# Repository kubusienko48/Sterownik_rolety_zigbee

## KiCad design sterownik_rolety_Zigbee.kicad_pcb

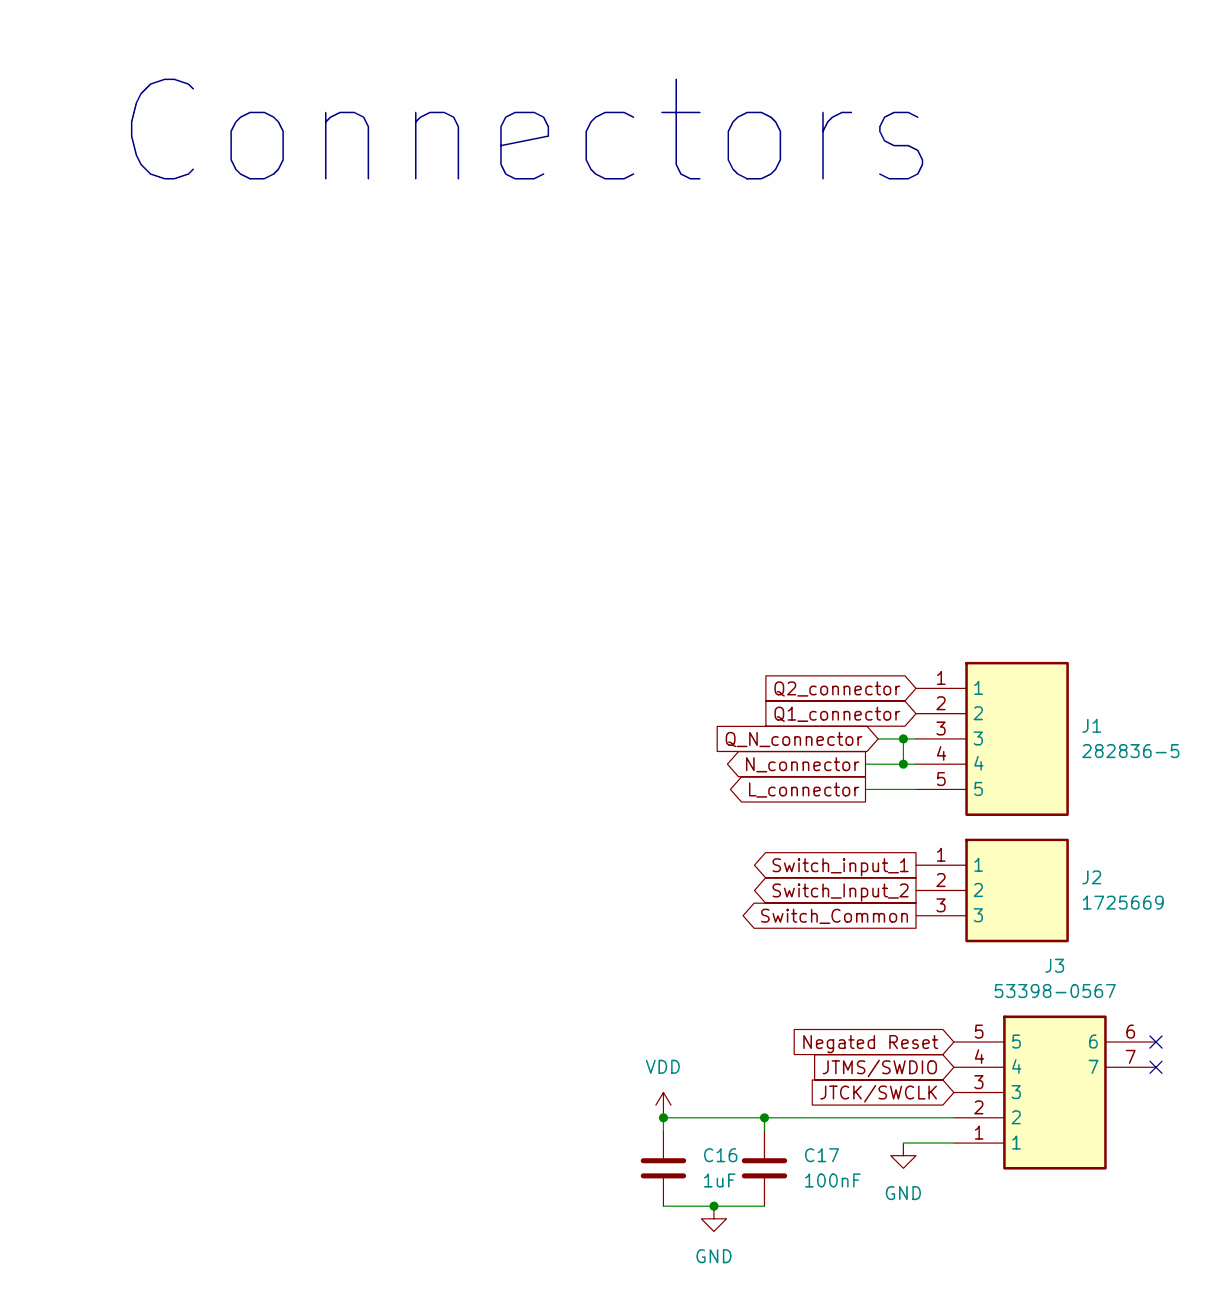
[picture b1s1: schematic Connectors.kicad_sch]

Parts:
C16: 1uF; C_0201_0603Metric
C17: 100nF; C_0201_0603Metric
J1: 282836-5; 2828365; Mouser Part Number 571-2828365
J2: 1725669; Mouser Part Number 651-1725669
J3: 53398-0567; 533980567; Mouser Part Number 538-53398-0567

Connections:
GND: C16.2, C17.2, J3.1; also elsewhere on the board
JTCK/SWCLK: J3.3; also elsewhere on the board
JTMS/SWDIO: J3.4; also elsewhere on the board
L_connector: J1.5; also elsewhere on the board
N_connector: J1.3, J1.4; also elsewhere on the board
Negated Reset: J3.5; also elsewhere on the board
Q1_connector: J1.2; also elsewhere on the board
Q2_connector: J1.1; also elsewhere on the board
Switch_Common: J2.3; also elsewhere on the board
Switch_Input_2: J2.2; also elsewhere on the board
Switch_input_1: J2.1; also elsewhere on the board
VDD: C16.1, C17.1, J3.2; also elsewhere on the board

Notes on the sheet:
Connectors

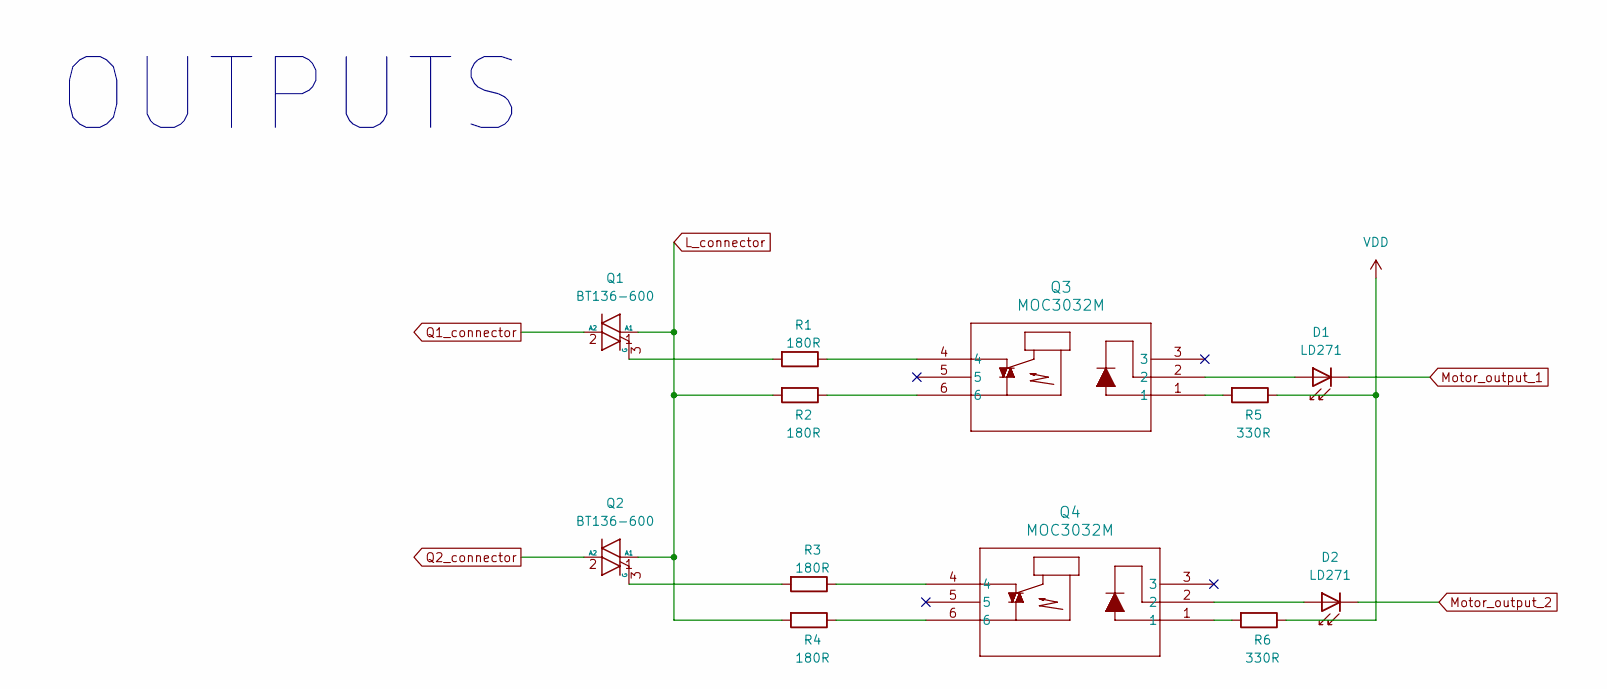
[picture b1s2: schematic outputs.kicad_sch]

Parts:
D1, D2: LD271; LED_D5.0mm_IRGrey
Q1, Q2: BT136-600; TO-220-3_Vertical
Q3, Q4: MOC3032M; DIP-6_W7.62mm
R1, R2, R3, R4: 180R; R_0201_0603Metric
R5, R6: 330R; R_0201_0603Metric

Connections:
L_connector: Q1.1 (A1), Q2.1 (A1), R2.2, R4.2; also elsewhere on the board
Motor_output_1: D1.1 (K); also elsewhere on the board
Motor_output_2: D2.1 (K); also elsewhere on the board
unnamed: D1.2 (A), Q3.2
unnamed: D2.2 (A), Q4.2
unnamed: Q1.3 (G), R1.2
unnamed: Q2.3 (G), R3.2
unnamed: Q3.1, R5.2
unnamed: Q3.4, R1.1
unnamed: Q3.6, R2.1
unnamed: Q4.1, R6.2
unnamed: Q4.4, R3.1
unnamed: Q4.6, R4.1
Q1_connector: Q1.2 (A2); also elsewhere on the board
Q2_connector: Q2.2 (A2); also elsewhere on the board
VDD: R5.1, R6.1; also elsewhere on the board

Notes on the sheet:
OUTPUTS

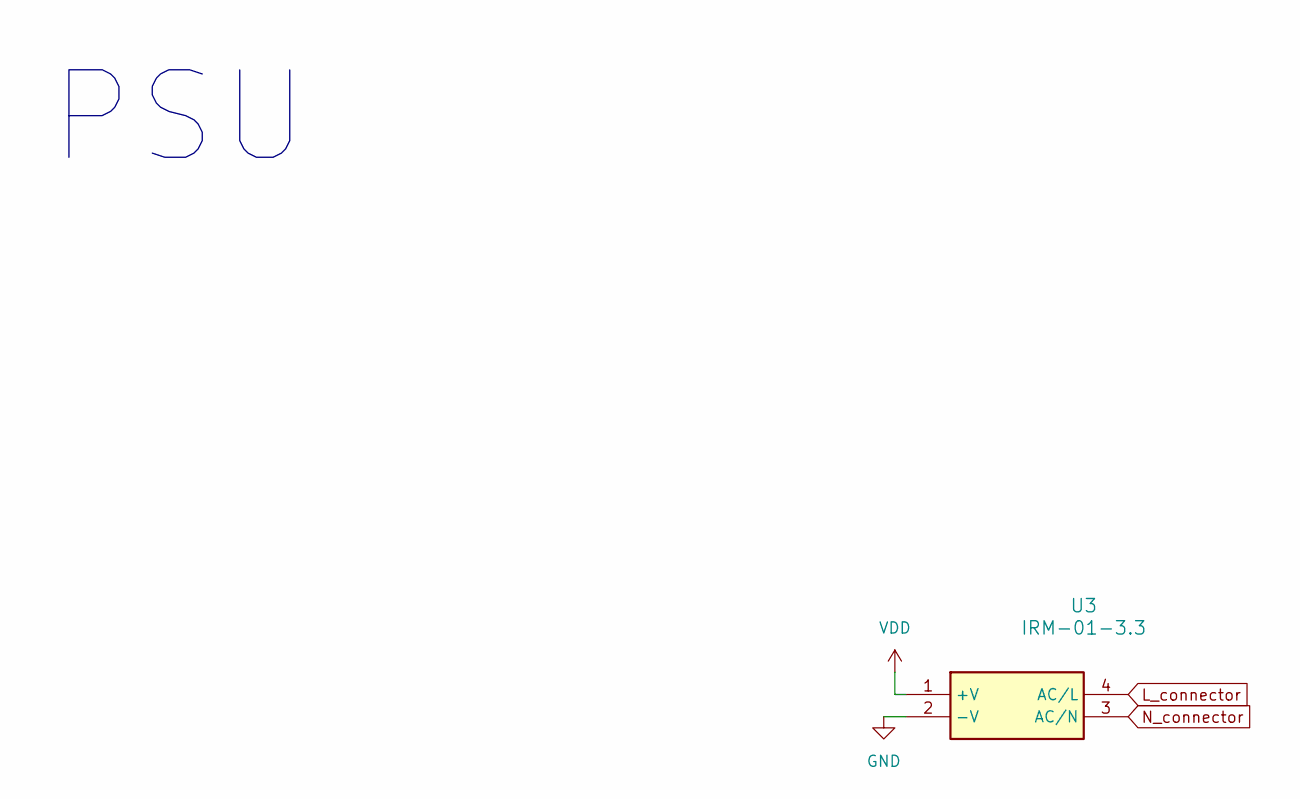
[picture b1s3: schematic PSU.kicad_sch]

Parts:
U3: IRM-01-3.3; IRM015; Mouser Part Number 709-IRM01-3.3

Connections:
GND: U3.2 (-V); also elsewhere on the board
L_connector: U3.4 (AC/L); also elsewhere on the board
N_connector: U3.3 (AC/N); also elsewhere on the board
VDD: U3.1 (+V); also elsewhere on the board

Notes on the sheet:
PSU

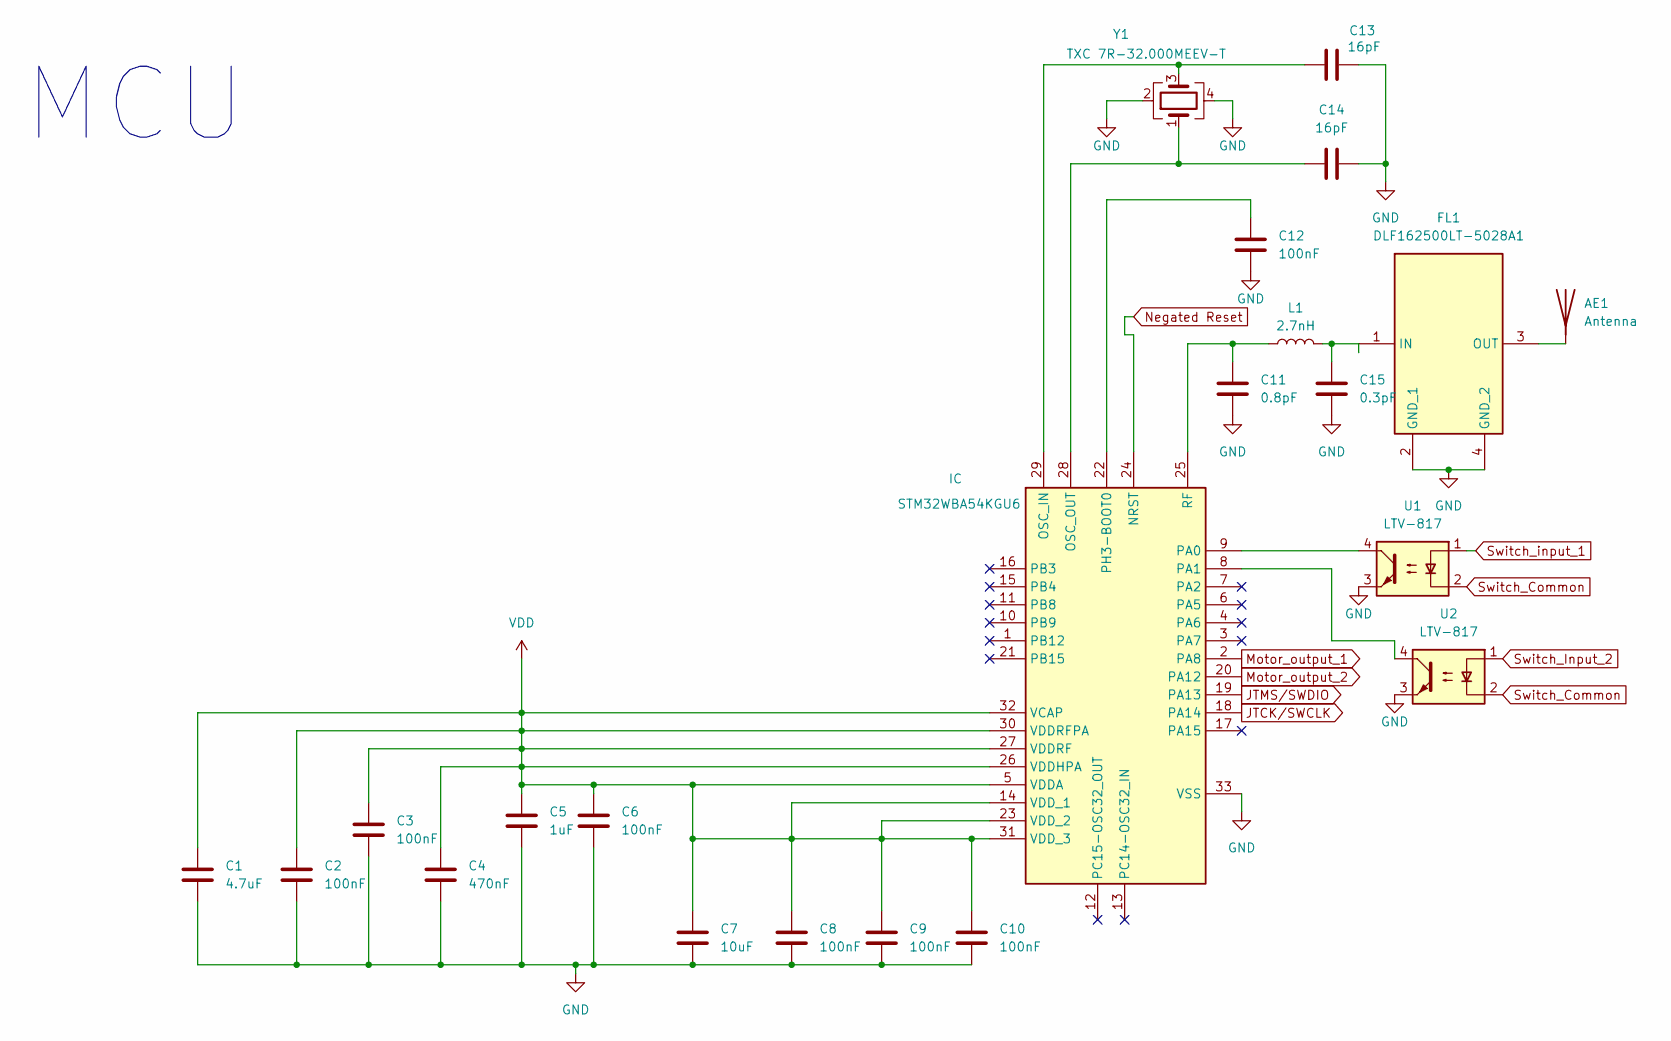
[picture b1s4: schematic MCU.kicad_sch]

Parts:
111111111: STM32WBA54KGU6; QFN50P500X500X60-33N-D; Mouser Part Number 511-STM32WBA54KGU6
AE1: Antenna
C1: 4.7uF; C_0201_0603Metric
C2, C3, C6, C8, C9, C10, C12: 100nF; C_0201_0603Metric
C4: 470nF; C_0201_0603Metric
C5: 1uF; C_0201_0603Metric
C7: 10uF; C_0201_0603Metric
C11: 0.8pF; C_0201_0603Metric
C13, C14: 16pF; C_0201_0603Metric
C15: 0.3pF; C_0201_0603Metric
FL1: DLF162500LT-5028A1; DLF162500LT5028A1; Mouser Part Number 810-DLF16250LT5028A1
L1: 2.7nH; L_0201_0603Metric
U1, U2: LTV-817; DIP-4_W7.62mm
Y1: TXC 7R-32.000MEEV-T

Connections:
GND: 111111111.33 (VSS), C1.2, C2.2, C3.2, C4.2, C5.2, C6.2, C7.2, C8.2, C9.2, C10.2, C11.2, C12.2, C13.1, C14.1, C15.2, FL1.2 (GND_1), FL1.4 (GND_2), U1.3, U2.3, Y1.2, Y1.4; also elsewhere on the board
JTCK/SWCLK: 111111111.18 (PA14); also elsewhere on the board
JTMS/SWDIO: 111111111.19 (PA13); also elsewhere on the board
Motor_output_1: 111111111.2 (PA8); also elsewhere on the board
Motor_output_2: 111111111.20 (PA12); also elsewhere on the board
Negated Reset: 111111111.24 (NRST); also elsewhere on the board
unnamed: 111111111.29 (OSC_IN), C13.2, Y1.3
unnamed: 111111111.28 (OSC_OUT), C14.2, Y1.1
unnamed: 111111111.9 (PA0), U1.4
unnamed: 111111111.8 (PA1), U2.4
unnamed: 111111111.22 (PH3-BOOT0), C12.1
unnamed: 111111111.25 (RF), C11.1, L1.1
unnamed: AE1.1, FL1.3 (OUT)
unnamed: C15.1, FL1.1 (IN), L1.2
Switch_Common: U1.2, U2.2; also elsewhere on the board
Switch_Input_2: U2.1; also elsewhere on the board
Switch_input_1: U1.1; also elsewhere on the board
VDD: 111111111.5 (VDDA), 111111111.14 (VDD_1), 111111111.23 (VDD_2), 111111111.26 (VDDHPA), 111111111.27 (VDDRF), 111111111.30 (VDDRFPA), 111111111.31 (VDD_3), 111111111.32 (VCAP), C1.1, C2.1, C3.1, C4.1, C5.1, C6.1, C7.1, C8.1, C9.1, C10.1; also elsewhere on the board

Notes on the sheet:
MCU

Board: 2 copper layers, 39 parts (0 on the bottom side), 31 nets, no tracks yet.

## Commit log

2024-11-30 Dodanie footprintów
2024-12-03 początkowe rozłożenie na PCB
2024-12-11 Update sterownik_rolety_Zigbee.kicad_pcb
    większe R i C, dodana antena
